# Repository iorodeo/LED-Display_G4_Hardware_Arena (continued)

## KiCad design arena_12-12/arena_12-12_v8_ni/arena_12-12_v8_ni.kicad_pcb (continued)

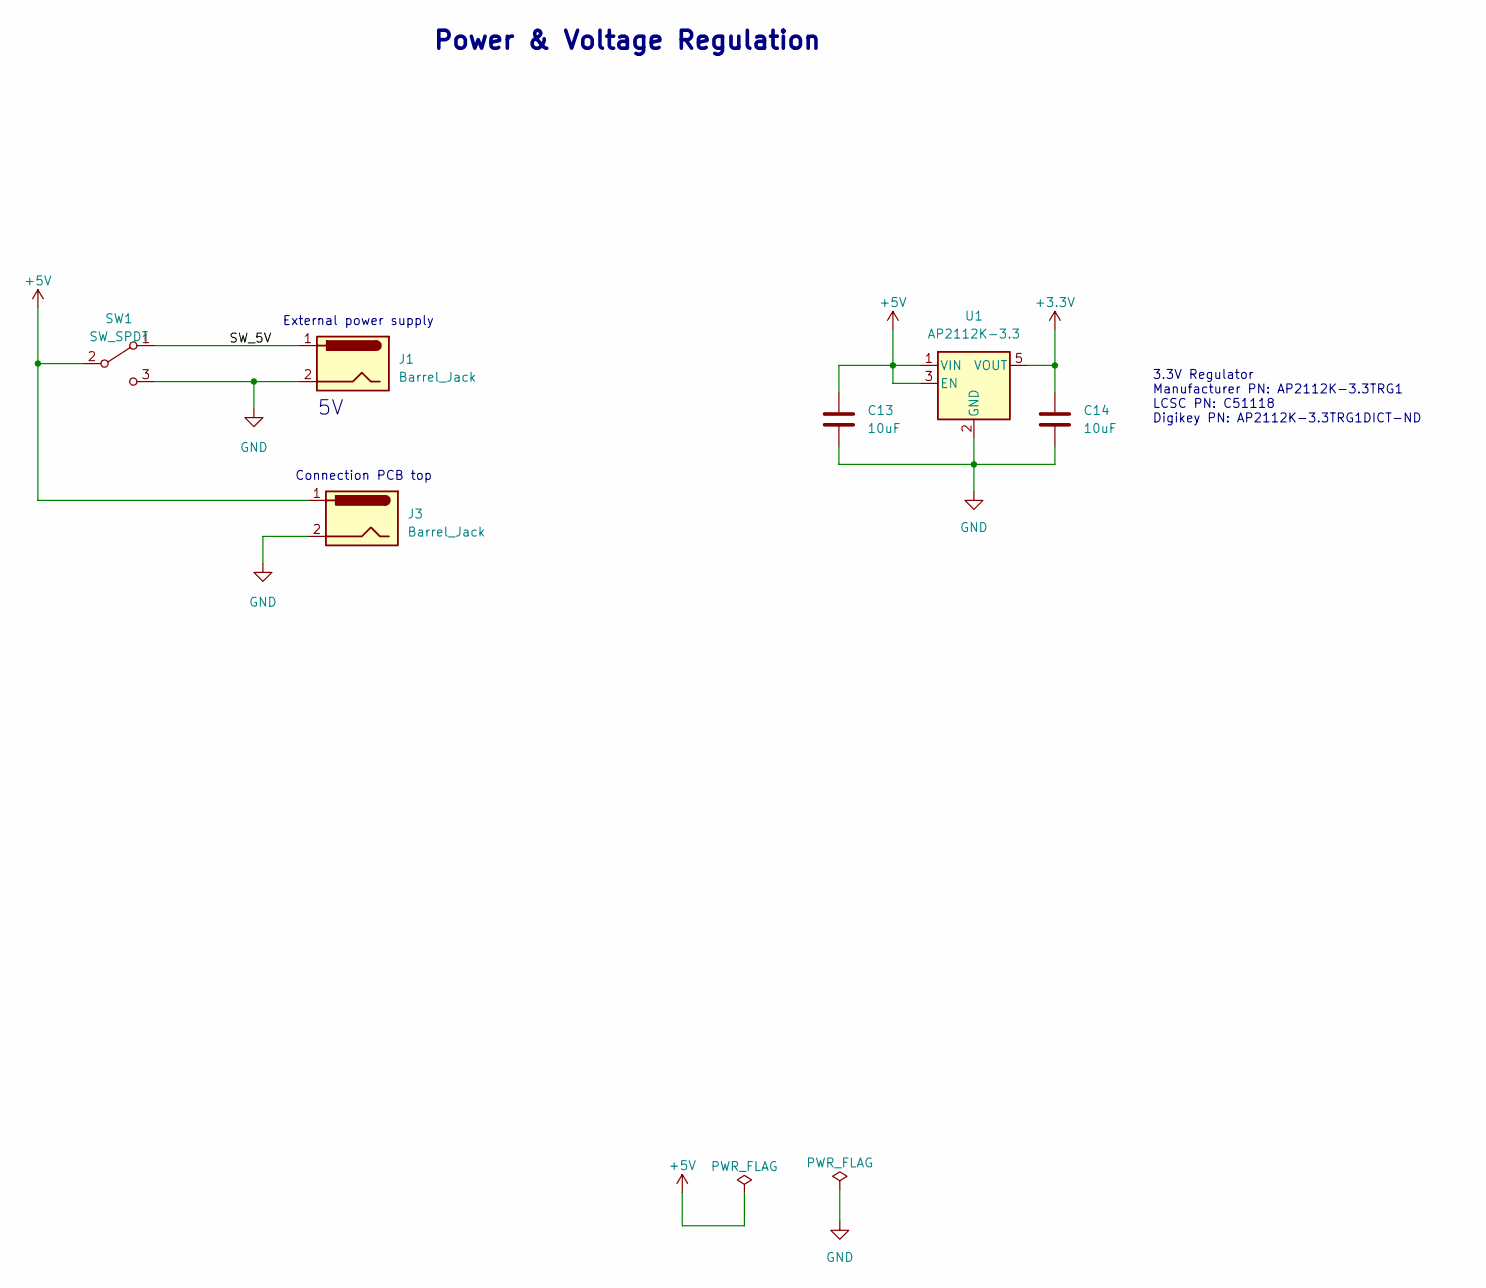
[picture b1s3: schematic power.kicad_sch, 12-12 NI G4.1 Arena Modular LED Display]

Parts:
C13, C14: 10uF; C_1206_3216Metric; MPN C3216X7R1C106KT000N; LCSC Part # C342827
J1, J3: Barrel_Jack; DCJACK_2PIN_HIGHCURRENT; MPN PJ-063AH; Digikey PN CP-063AH-ND
SW1: SW_SPDT; slide_switch; MPN L102021ML04Q; Digikey PN CKC5102-ND
U1: AP2112K-3.3; SOT-23-5; MPN AP2112K-3.3TRG1; Digikey PN AP2112K-3.3TRG1DICT-ND

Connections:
+3.3V: C14.1, U1.5 (VOUT); also elsewhere on the board
+5V: C13.1, J3.1, SW1.2 (B), U1.1 (VIN), U1.3 (EN); also elsewhere on the board
/Power & Voltage Regulators/SW_5V: J1.1, SW1.1 (A)
GND: C13.2, C14.2, J1.2, J3.2, SW1.3 (C), U1.2 (GND); also elsewhere on the board

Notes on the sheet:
External power supply
3.3V Regulator Manufacturer PN: AP2112K-3.3TRG1 LCSC PN: C51118 Digikey PN: AP2112K-3.3TRG1DICT-ND
Power & Voltage Regulation
Connection PCB top

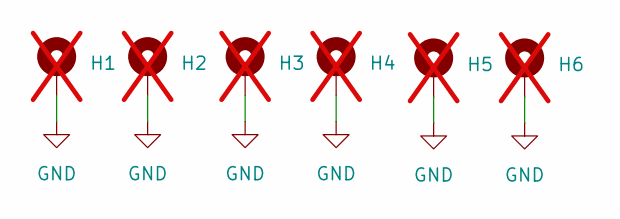
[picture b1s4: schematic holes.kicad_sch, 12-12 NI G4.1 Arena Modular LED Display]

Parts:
H1, H2, H3, H4, H5, H6: MountingHole_Pad; MountingHole_4.5mm_Pad; not fitted

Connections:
GND: H1.1, H2.1, H3.1, H4.1, H5.1, H6.1; also elsewhere on the board

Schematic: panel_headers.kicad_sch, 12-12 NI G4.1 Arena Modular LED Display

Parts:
C1, C2, C3, C4, C5, C6, C7, C8, C9, C10, C11, C12: 100uF; C_1210_3225Metric; MPN HGC1210R5107M160NSVK; LCSC Part # C7432790
C35, C36, C37, C38, C39, C40, C41, C42, C43, C44, C45, C46, C47, C48, C49, C50, C51, C52, C53, C54, C55, C56, C57, C58, C59, C60, C61, C62, C63, C64, C65, C66, C67, C68, C69, C70, C71, C72, C73, C74, C75, C76, C77, C78, C79, C80, C81, C82, C83, C84, C85, C86, C87, C88, C89, C90, C91, C92, C93, C94, C95, C96, C97, C98, C99, C100, C101, C102, C103, C104, C105, C106: 0.1uF; C_0402_1005Metric; MPN CL05B104KO5NNNC; LCSC Part # C1525
P1, P2, P3, P4, P5, P6, P7, P8, P9, P10, P11, P12: CONN15; HEADER_TOP; MPN PPPC151LFBN-RC; Digikey PN S7048-ND
Q1: MOSFET_NCHAN; SOT-23-3; MPN ME2306D; LCSC Part # C165220
R163, R164, R165, R166, R167, R168, R169, R170, R171, R172, R173, R174, R175, R176, R177, R178, R179, R180, R181, R182, R183, R184, R185, R186, R187, R188, R189, R190, R191, R192, R193, R194, R195, R196, R197, R198, R199, R200, R201, R202, R203, R204, R205, R206, R207, R208, R209, R210, R211, R212, R213, R214, R215, R216, R217, R218, R219, R220, R221, R222, R223, R224, R225, R226, R227, R228, R229, R230, R231, R232, R233, R234, R235, R236, R237, R238, R239, R240, R241, R242, R243, R244, R245, R246, R247, R248, R249, R250, R251, R252, R253, R254, R255, R256, R257, R258, R259, R260, R261, R262, R263, R264, R265, R266, R267, R268, R269, R270, R271, R272, R273, R274, R275, R276, R277, R278, R279, R280, R281, R282, R283, R284, R285, R286, R287, R288, R289, R290, R291, R292, R293, R294, R295, R296, R297, R298, R299, R300, R301, R302, R303, R304, R305, R306: 33; R_0402_1005Metric; MPN 0402WGF330JTCE; LCSC Part # C25105
R307: 20k; R_0402_1005Metric; MPN 0402WGF2002TCE; LCSC Part # C25765
R308: 200; R_0402_1005Metric; MPN 0402WGF2000TCE; LCSC Part # C25087
U39, U40, U41, U42, U43, U44, U45, U46, U47, U48, U49, U50, U51, U52, U53, U54, U55, U56, U57, U58, U59, U60, U61, U62, U63, U64, U65, U66, U67, U68, U69, U70, U71, U72, U73, U74, U75, U76, U77, U78, U79, U80, U81, U82, U83, U84, U85, U86, U87, U88, U89, U90, U91, U92, U93, U94, U95, U96, U97, U98, U99, U100, U101, U102, U103, U104, U105, U106, U107, U108, U109, U110: 74LVC2G17; SOT-23-6; MPN SN74LVC2G17DBVR; Digikey PN 296-SN74LVC2G17DBVRTR-ND

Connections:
+5V: C1.1, C2.1, C3.1, C4.1, C5.1, C6.1, C7.1, C8.1, C9.1, C10.1, C11.1, C12.1, C35.1, C36.1, C37.1, C38.1, C39.1, C40.1, C41.1, C42.1, C43.1, C44.1, C45.1, C46.1, C47.1, C48.1, C49.1, C50.1, C51.1, C52.1, C53.1, C54.1, C55.1, C56.1, C57.1, C58.1, C59.1, C60.1, C61.1, C62.1, C63.1, C64.1, C65.1, C66.1, C67.1, C68.1, C69.1, C70.1, C71.1, C72.1, C73.1, C74.1, C75.1, C76.1, C77.1, C78.1, C79.1, C80.1, C81.1, C82.1, C83.1, C84.1, C85.1, C86.1, C87.1, C88.1, C89.1, C90.1, C91.1, C92.1, C93.1, C94.1, C95.1, C96.1, C97.1, C98.1, C99.1, C100.1, C101.1, C102.1, C103.1, C104.1, C105.1, C106.1, P1.1, P2.1, P3.1, P4.1, P5.1, P6.1, P7.1, P8.1, P9.1, P10.1, P11.1, P12.1, U39.5 (VCC), U40.5 (VCC), U41.5 (VCC), U42.5 (VCC), U43.5 (VCC), U44.5 (VCC), U45.5 (VCC), U46.5 (VCC), U47.5 (VCC), U48.5 (VCC), U49.5 (VCC), U50.5 (VCC), U51.5 (VCC), U52.5 (VCC), U53.5 (VCC), U54.5 (VCC), U55.5 (VCC), U56.5 (VCC), U57.5 (VCC), U58.5 (VCC), U59.5 (VCC), U60.5 (VCC), U61.5 (VCC), U62.5 (VCC), U63.5 (VCC), U64.5 (VCC), U65.5 (VCC), U66.5 (VCC), U67.5 (VCC), U68.5 (VCC), U69.5 (VCC), U70.5 (VCC), U71.5 (VCC), U72.5 (VCC), U73.5 (VCC), U74.5 (VCC), U75.5 (VCC), U76.5 (VCC), U77.5 (VCC), U78.5 (VCC), U79.5 (VCC), U80.5 (VCC), U81.5 (VCC), U82.5 (VCC), U83.5 (VCC), U84.5 (VCC), U85.5 (VCC), U86.5 (VCC), U87.5 (VCC), U88.5 (VCC), U89.5 (VCC), U90.5 (VCC), U91.5 (VCC), U92.5 (VCC), U93.5 (VCC), U94.5 (VCC), U95.5 (VCC), U96.5 (VCC), U97.5 (VCC), U98.5 (VCC), U99.5 (VCC), U100.5 (VCC), U101.5 (VCC), U102.5 (VCC), U103.5 (VCC), U104.5 (VCC), U105.5 (VCC), U106.5 (VCC), U107.5 (VCC), U108.5 (VCC), U109.5 (VCC), U110.5 (VCC); also elsewhere on the board
/Level Shifters/PAN5V.CS_0_P01: U40.3; also elsewhere on the board
/Level Shifters/PAN5V.CS_0_P02: U46.3; also elsewhere on the board
/Level Shifters/PAN5V.CS_0_P03: U52.3; also elsewhere on the board
/Level Shifters/PAN5V.CS_0_P04: U58.3; also elsewhere on the board
/Level Shifters/PAN5V.CS_0_P05: U64.3; also elsewhere on the board
/Level Shifters/PAN5V.CS_0_P06: U70.3; also elsewhere on the board
/Level Shifters/PAN5V.CS_0_P07: U76.3; also elsewhere on the board
/Level Shifters/PAN5V.CS_0_P08: U82.3; also elsewhere on the board
/Level Shifters/PAN5V.CS_0_P09: U88.3; also elsewhere on the board
/Level Shifters/PAN5V.CS_0_P10: U94.3; also elsewhere on the board
/Level Shifters/PAN5V.CS_0_P11: U100.3; also elsewhere on the board
/Level Shifters/PAN5V.CS_0_P12: U106.3; also elsewhere on the board
/Level Shifters/PAN5V.CS_1_P01: U40.1; also elsewhere on the board
/Level Shifters/PAN5V.CS_1_P02: U46.1; also elsewhere on the board
/Level Shifters/PAN5V.CS_1_P03: U52.1; also elsewhere on the board
/Level Shifters/PAN5V.CS_1_P04: U58.1; also elsewhere on the board
/Level Shifters/PAN5V.CS_1_P05: U64.1; also elsewhere on the board
/Level Shifters/PAN5V.CS_1_P06: U70.1; also elsewhere on the board
/Level Shifters/PAN5V.CS_1_P07: U76.1; also elsewhere on the board
/Level Shifters/PAN5V.CS_1_P08: U82.1; also elsewhere on the board
/Level Shifters/PAN5V.CS_1_P09: U88.1; also elsewhere on the board
/Level Shifters/PAN5V.CS_1_P10: U94.1; also elsewhere on the board
/Level Shifters/PAN5V.CS_1_P11: U100.1; also elsewhere on the board
/Level Shifters/PAN5V.CS_1_P12: U106.1; also elsewhere on the board
/Level Shifters/PAN5V.CS_2_P01: U41.3; also elsewhere on the board
/Level Shifters/PAN5V.CS_2_P02: U47.3; also elsewhere on the board
/Level Shifters/PAN5V.CS_2_P03: U53.3; also elsewhere on the board
/Level Shifters/PAN5V.CS_2_P04: U59.3; also elsewhere on the board
/Level Shifters/PAN5V.CS_2_P05: U65.3; also elsewhere on the board
/Level Shifters/PAN5V.CS_2_P06: U71.3; also elsewhere on the board
/Level Shifters/PAN5V.CS_2_P07: U77.3; also elsewhere on the board
/Level Shifters/PAN5V.CS_2_P08: U83.3; also elsewhere on the board
/Level Shifters/PAN5V.CS_2_P09: U89.3; also elsewhere on the board
/Level Shifters/PAN5V.CS_2_P10: U95.3; also elsewhere on the board
/Level Shifters/PAN5V.CS_2_P11: U101.3; also elsewhere on the board
/Level Shifters/PAN5V.CS_2_P12: U107.3; also elsewhere on the board
/Level Shifters/PAN5V.CS_3_P01: U41.1; also elsewhere on the board
/Level Shifters/PAN5V.CS_3_P02: U47.1; also elsewhere on the board
/Level Shifters/PAN5V.CS_3_P03: U53.1; also elsewhere on the board
/Level Shifters/PAN5V.CS_3_P04: U59.1; also elsewhere on the board
/Level Shifters/PAN5V.CS_3_P05: U65.1; also elsewhere on the board
/Level Shifters/PAN5V.CS_3_P06: U71.1; also elsewhere on the board
/Level Shifters/PAN5V.CS_3_P07: U77.1; also elsewhere on the board
/Level Shifters/PAN5V.CS_3_P08: U83.1; also elsewhere on the board
/Level Shifters/PAN5V.CS_3_P09: U89.1; also elsewhere on the board
/Level Shifters/PAN5V.CS_3_P10: U95.1; also elsewhere on the board
/Level Shifters/PAN5V.CS_3_P11: U101.1; also elsewhere on the board
/Level Shifters/PAN5V.CS_3_P12: U107.1; also elsewhere on the board
/Level Shifters/PAN5V.CS_4_P01: U42.3; also elsewhere on the board
/Level Shifters/PAN5V.CS_4_P02: U48.3; also elsewhere on the board
/Level Shifters/PAN5V.CS_4_P03: U54.3; also elsewhere on the board
/Level Shifters/PAN5V.CS_4_P04: U60.3; also elsewhere on the board
/Level Shifters/PAN5V.CS_4_P05: U66.3; also elsewhere on the board
/Level Shifters/PAN5V.CS_4_P06: U72.3; also elsewhere on the board
/Level Shifters/PAN5V.CS_4_P07: U78.3; also elsewhere on the board
/Level Shifters/PAN5V.CS_4_P08: U84.3; also elsewhere on the board
/Level Shifters/PAN5V.CS_4_P09: U90.3; also elsewhere on the board
/Level Shifters/PAN5V.CS_4_P10: U96.3; also elsewhere on the board
/Level Shifters/PAN5V.CS_4_P11: U102.3; also elsewhere on the board
/Level Shifters/PAN5V.CS_4_P12: U108.3; also elsewhere on the board
/Level Shifters/PAN5V.CS_5_P01: U42.1; also elsewhere on the board
/Level Shifters/PAN5V.CS_5_P02: U48.1; also elsewhere on the board
/Level Shifters/PAN5V.CS_5_P03: U54.1; also elsewhere on the board
/Level Shifters/PAN5V.CS_5_P04: U60.1; also elsewhere on the board
/Level Shifters/PAN5V.CS_5_P05: U66.1; also elsewhere on the board
/Level Shifters/PAN5V.CS_5_P06: U72.1; also elsewhere on the board
/Level Shifters/PAN5V.CS_5_P07: U78.1; also elsewhere on the board
/Level Shifters/PAN5V.CS_5_P08: U84.1; also elsewhere on the board
/Level Shifters/PAN5V.CS_5_P09: U90.1; also elsewhere on the board
/Level Shifters/PAN5V.CS_5_P10: U96.1; also elsewhere on the board
/Level Shifters/PAN5V.CS_5_P11: U102.1; also elsewhere on the board
/Level Shifters/PAN5V.CS_5_P12: U108.1; also elsewhere on the board
/Level Shifters/PAN5V.CS_6_P01: U43.3; also elsewhere on the board
/Level Shifters/PAN5V.CS_6_P02: U49.3; also elsewhere on the board
/Level Shifters/PAN5V.CS_6_P03: U55.3; also elsewhere on the board
/Level Shifters/PAN5V.CS_6_P04: U61.3; also elsewhere on the board
/Level Shifters/PAN5V.CS_6_P05: U67.3; also elsewhere on the board
/Level Shifters/PAN5V.CS_6_P06: U73.3; also elsewhere on the board
/Level Shifters/PAN5V.CS_6_P07: U79.3; also elsewhere on the board
/Level Shifters/PAN5V.CS_6_P08: U85.3; also elsewhere on the board
/Level Shifters/PAN5V.CS_6_P09: U91.3; also elsewhere on the board
/Level Shifters/PAN5V.CS_6_P10: U97.3; also elsewhere on the board
/Level Shifters/PAN5V.CS_6_P11: U103.3; also elsewhere on the board
/Level Shifters/PAN5V.CS_6_P12: U109.3; also elsewhere on the board
/Level Shifters/PAN5V.CS_7_P01: U43.1; also elsewhere on the board
/Level Shifters/PAN5V.CS_7_P02: U49.1; also elsewhere on the board
/Level Shifters/PAN5V.CS_7_P03: U55.1; also elsewhere on the board
/Level Shifters/PAN5V.CS_7_P04: U61.1; also elsewhere on the board
/Level Shifters/PAN5V.CS_7_P05: U67.1; also elsewhere on the board
/Level Shifters/PAN5V.CS_7_P06: U73.1; also elsewhere on the board
/Level Shifters/PAN5V.CS_7_P07: U79.1; also elsewhere on the board
/Level Shifters/PAN5V.CS_7_P08: U85.1; also elsewhere on the board
/Level Shifters/PAN5V.CS_7_P09: U91.1; also elsewhere on the board
/Level Shifters/PAN5V.CS_7_P10: U97.1; also elsewhere on the board
/Level Shifters/PAN5V.CS_7_P11: U103.1; also elsewhere on the board
/Level Shifters/PAN5V.CS_7_P12: U109.1; also elsewhere on the board
/Level Shifters/PAN5V.EXT_INT: U44.3, U50.3, U56.3, U62.3, U68.3, U74.3, U80.3, U86.3, U92.3, U98.3, U104.3, U110.3; also elsewhere on the board
/Level Shifters/PAN5V.MISO_00: R165.1; also elsewhere on the board
/Level Shifters/PAN5V.MISO_01: R177.1; also elsewhere on the board
/Level Shifters/PAN5V.MISO_02: R189.1; also elsewhere on the board
/Level Shifters/PAN5V.MISO_03: R201.1; also elsewhere on the board
/Level Shifters/PAN5V.MISO_04: R213.1; also elsewhere on the board
/Level Shifters/PAN5V.MISO_05: R225.1; also elsewhere on the board
/Level Shifters/PAN5V.MISO_06: R237.1; also elsewhere on the board
/Level Shifters/PAN5V.MISO_07: R249.1; also elsewhere on the board
/Level Shifters/PAN5V.MISO_08: R261.1; also elsewhere on the board
/Level Shifters/PAN5V.MISO_09: R273.1; also elsewhere on the board
/Level Shifters/PAN5V.MISO_10: R285.1; also elsewhere on the board
/Level Shifters/PAN5V.MISO_11: R297.1; also elsewhere on the board
/Level Shifters/PAN5V.MOSI_00: U39.1; also elsewhere on the board
/Level Shifters/PAN5V.MOSI_01: U45.1; also elsewhere on the board
/Level Shifters/PAN5V.MOSI_02: U51.1; also elsewhere on the board
/Level Shifters/PAN5V.MOSI_03: U57.1; also elsewhere on the board
/Level Shifters/PAN5V.MOSI_04: U63.1; also elsewhere on the board
/Level Shifters/PAN5V.MOSI_05: U69.1; also elsewhere on the board
/Level Shifters/PAN5V.MOSI_06: U75.1; also elsewhere on the board
/Level Shifters/PAN5V.MOSI_07: U81.1; also elsewhere on the board
/Level Shifters/PAN5V.MOSI_08: U87.1; also elsewhere on the board
/Level Shifters/PAN5V.MOSI_09: U93.1; also elsewhere on the board
/Level Shifters/PAN5V.MOSI_10: U99.1; also elsewhere on the board
/Level Shifters/PAN5V.MOSI_11: U105.1; also elsewhere on the board
/Level Shifters/PAN5V.RESET: R308.2; also elsewhere on the board
/Level Shifters/PAN5V.SCK_0_H1: U39.3; also elsewhere on the board
/Level Shifters/PAN5V.SCK_0_H2: U75.3; also elsewhere on the board
/Level Shifters/PAN5V.SCK_1_H1: U45.3; also elsewhere on the board
/Level Shifters/PAN5V.SCK_1_H2: U81.3; also elsewhere on the board
/Level Shifters/PAN5V.SCK_2_H1: U51.3; also elsewhere on the board
/Level Shifters/PAN5V.SCK_2_H2: U87.3; also elsewhere on the board
/Level Shifters/PAN5V.SCK_3_H1: U57.3; also elsewhere on the board
/Level Shifters/PAN5V.SCK_3_H2: U93.3; also elsewhere on the board
/Level Shifters/PAN5V.SCK_4_H1: U63.3; also elsewhere on the board
/Level Shifters/PAN5V.SCK_4_H2: U99.3; also elsewhere on the board
/Level Shifters/PAN5V.SCK_5_H1: U69.3; also elsewhere on the board
/Level Shifters/PAN5V.SCK_5_H2: U105.3; also elsewhere on the board
/Panel Headers/CS_00_P01: P1.7, R166.2
/Panel Headers/CS_00_P02: P2.7, R178.2
/Panel Headers/CS_00_P03: P3.7, R190.2
/Panel Headers/CS_00_P04: P4.7, R202.2
/Panel Headers/CS_00_P05: P5.7, R214.2
/Panel Headers/CS_00_P06: P6.7, R226.2
/Panel Headers/CS_00_P07: P7.7, R238.2
/Panel Headers/CS_00_P08: P8.7, R250.2
/Panel Headers/CS_00_P09: P9.7, R262.2
/Panel Headers/CS_00_P10: P10.7, R274.2
/Panel Headers/CS_00_P11: P11.7, R286.2
/Panel Headers/CS_00_P12: P12.7, R298.2
/Panel Headers/CS_01_P01: P1.8, R167.2
/Panel Headers/CS_01_P02: P2.8, R179.2
/Panel Headers/CS_01_P03: P3.8, R191.2
/Panel Headers/CS_01_P04: P4.8, R203.2
/Panel Headers/CS_01_P05: P5.8, R215.2
/Panel Headers/CS_01_P06: P6.8, R227.2
/Panel Headers/CS_01_P07: P7.8, R239.2
/Panel Headers/CS_01_P08: P8.8, R251.2
/Panel Headers/CS_01_P09: P9.8, R263.2
/Panel Headers/CS_01_P10: P10.8, R275.2
/Panel Headers/CS_01_P11: P11.8, R287.2
/Panel Headers/CS_01_P12: P12.8, R299.2
/Panel Headers/CS_02_P01: P1.9, R168.2
/Panel Headers/CS_02_P02: P2.9, R180.2
/Panel Headers/CS_02_P03: P3.9, R192.2
/Panel Headers/CS_02_P04: P4.9, R204.2
/Panel Headers/CS_02_P05: P5.9, R216.2
/Panel Headers/CS_02_P06: P6.9, R228.2
/Panel Headers/CS_02_P07: P7.9, R240.2
/Panel Headers/CS_02_P08: P8.9, R252.2
/Panel Headers/CS_02_P09: P9.9, R264.2
/Panel Headers/CS_02_P10: P10.9, R276.2
/Panel Headers/CS_02_P11: P11.9, R288.2
/Panel Headers/CS_02_P12: P12.9, R300.2
/Panel Headers/CS_03_P01: P1.10, R169.2
/Panel Headers/CS_03_P02: P2.10, R181.2
/Panel Headers/CS_03_P03: P3.10, R193.2
/Panel Headers/CS_03_P04: P4.10, R205.2
/Panel Headers/CS_03_P05: P5.10, R217.2
/Panel Headers/CS_03_P06: P6.10, R229.2
/Panel Headers/CS_03_P07: P7.10, R241.2
/Panel Headers/CS_03_P08: P8.10, R253.2
/Panel Headers/CS_03_P09: P9.10, R265.2
/Panel Headers/CS_03_P10: P10.10, R277.2
/Panel Headers/CS_03_P11: P11.10, R289.2
/Panel Headers/CS_03_P12: P12.10, R301.2
/Panel Headers/CS_04_P01: P1.11, R170.2
/Panel Headers/CS_04_P02: P2.11, R182.2
/Panel Headers/CS_04_P03: P3.11, R194.2
/Panel Headers/CS_04_P04: P4.11, R206.2
/Panel Headers/CS_04_P05: P5.11, R218.2
/Panel Headers/CS_04_P06: P6.11, R230.2
/Panel Headers/CS_04_P07: P7.11, R242.2
/Panel Headers/CS_04_P08: P8.11, R254.2
/Panel Headers/CS_04_P09: P9.11, R266.2
/Panel Headers/CS_04_P10: P10.11, R278.2
/Panel Headers/CS_04_P11: P11.11, R290.2
/Panel Headers/CS_04_P12: P12.11, R302.2
/Panel Headers/CS_05_P01: P1.12, R171.2
/Panel Headers/CS_05_P02: P2.12, R183.2
/Panel Headers/CS_05_P03: P3.12, R195.2
/Panel Headers/CS_05_P04: P4.12, R207.2
/Panel Headers/CS_05_P05: P5.12, R219.2
/Panel Headers/CS_05_P06: P6.12, R231.2
/Panel Headers/CS_05_P07: P7.12, R243.2
/Panel Headers/CS_05_P08: P8.12, R255.2
/Panel Headers/CS_05_P09: P9.12, R267.2
/Panel Headers/CS_05_P10: P10.12, R279.2
/Panel Headers/CS_05_P11: P11.12, R291.2
/Panel Headers/CS_05_P12: P12.12, R303.2
/Panel Headers/CS_06_P01: P1.13, R172.2
/Panel Headers/CS_06_P02: P2.13, R184.2
/Panel Headers/CS_06_P03: P3.13, R196.2
/Panel Headers/CS_06_P04: P4.13, R208.2
/Panel Headers/CS_06_P05: P5.13, R220.2
/Panel Headers/CS_06_P06: P6.13, R232.2
/Panel Headers/CS_06_P07: P7.13, R244.2
/Panel Headers/CS_06_P08: P8.13, R256.2
/Panel Headers/CS_06_P09: P9.13, R268.2
/Panel Headers/CS_06_P10: P10.13, R280.2
/Panel Headers/CS_06_P11: P11.13, R292.2
/Panel Headers/CS_06_P12: P12.13, R304.2
/Panel Headers/CS_07_P01: P1.14, R173.2
/Panel Headers/CS_07_P02: P2.14, R185.2
/Panel Headers/CS_07_P03: P3.14, R197.2
/Panel Headers/CS_07_P04: P4.14, R209.2
/Panel Headers/CS_07_P05: P5.14, R221.2
/Panel Headers/CS_07_P06: P6.14, R233.2
/Panel Headers/CS_07_P07: P7.14, R245.2
/Panel Headers/CS_07_P08: P8.14, R257.2
/Panel Headers/CS_07_P09: P9.14, R269.2
/Panel Headers/CS_07_P10: P10.14, R281.2
/Panel Headers/CS_07_P11: P11.14, R293.2
/Panel Headers/CS_07_P12: P12.14, R305.2
/Panel Headers/EXT_INT_P01: P1.15, R174.2
/Panel Headers/EXT_INT_P02: P2.15, R186.2
/Panel Headers/EXT_INT_P03: P3.15, R198.2
/Panel Headers/EXT_INT_P04: P4.15, R210.2
/Panel Headers/EXT_INT_P05: P5.15, R222.2
/Panel Headers/EXT_INT_P06: P6.15, R234.2
/Panel Headers/EXT_INT_P07: P7.15, R246.2
/Panel Headers/EXT_INT_P08: P8.15, R258.2
/Panel Headers/EXT_INT_P09: P9.15, R270.2
/Panel Headers/EXT_INT_P10: P10.15, R282.2
/Panel Headers/EXT_INT_P11: P11.15, R294.2
/Panel Headers/EXT_INT_P12: P12.15, R306.2
/Panel Headers/MISO_00_P01: P1.6, R165.2
/Panel Headers/MISO_01_P02: P2.6, R177.2
/Panel Headers/MISO_02_P03: P3.6, R189.2
/Panel Headers/MISO_03_P04: P4.6, R201.2
/Panel Headers/MISO_04_P05: P5.6, R213.2
/Panel Headers/MISO_05_P06: P6.6, R225.2
/Panel Headers/MISO_06_P07: P7.6, R237.2
/Panel Headers/MISO_07_P08: P8.6, R249.2
/Panel Headers/MISO_08_P09: P9.6, R261.2
/Panel Headers/MISO_09_P10: P10.6, R273.2
/Panel Headers/MISO_10_P11: P11.6, R285.2
/Panel Headers/MISO_11_P12: P12.6, R297.2
/Panel Headers/MOSI_00_P01: P1.5, R164.2
/Panel Headers/MOSI_01_P02: P2.5, R176.2
/Panel Headers/MOSI_02_P03: P3.5, R188.2
/Panel Headers/MOSI_03_P04: P4.5, R200.2
/Panel Headers/MOSI_04_P05: P5.5, R212.2
/Panel Headers/MOSI_05_P06: P6.5, R224.2
/Panel Headers/MOSI_06_P07: P7.5, R236.2
/Panel Headers/MOSI_07_P08: P8.5, R248.2
/Panel Headers/MOSI_08_P09: P9.5, R260.2
/Panel Headers/MOSI_09_P10: P10.5, R272.2
/Panel Headers/MOSI_10_P11: P11.5, R284.2
/Panel Headers/MOSI_11_P12: P12.5, R296.2
/Panel Headers/RESET: P1.3, P2.3, P3.3, P4.3, P5.3, P6.3, P7.3, P8.3, P9.3, P10.3, P11.3, P12.3, Q1.3 (D)
/Panel Headers/SCK_0_H1_P01: P1.4, R163.2
/Panel Headers/SCK_0_H2_P07: P7.4, R235.2
/Panel Headers/SCK_1_H1_P02: P2.4, R175.2
/Panel Headers/SCK_1_H2_P08: P8.4, R247.2
/Panel Headers/SCK_2_H1_P03: P3.4, R187.2
/Panel Headers/SCK_2_H2_P09: P9.4, R259.2
/Panel Headers/SCK_3_H1_P04: P4.4, R199.2
/Panel Headers/SCK_3_H2_P10: P10.4, R271.2
/Panel Headers/SCK_4_H1_P05: P5.4, R211.2
/Panel Headers/SCK_4_H2_P11: P11.4, R283.2
/Panel Headers/SCK_5_H1_P06: P6.4, R223.2
/Panel Headers/SCK_5_H2_P12: P12.4, R295.2
GND: C1.2, C2.2, C3.2, C4.2, C5.2, C6.2, C7.2, C8.2, C9.2, C10.2, C11.2, C12.2, C35.2, C36.2, C37.2, C38.2, C39.2, C40.2, C41.2, C42.2, C43.2, C44.2, C45.2, C46.2, C47.2, C48.2, C49.2, C50.2, C51.2, C52.2, C53.2, C54.2, C55.2, C56.2, C57.2, C58.2, C59.2, C60.2, C61.2, C62.2, C63.2, C64.2, C65.2, C66.2, C67.2, C68.2, C69.2, C70.2, C71.2, C72.2, C73.2, C74.2, C75.2, C76.2, C77.2, C78.2, C79.2, C80.2, C81.2, C82.2, C83.2, C84.2, C85.2, C86.2, C87.2, C88.2, C89.2, C90.2, C91.2, C92.2, C93.2, C94.2, C95.2, C96.2, C97.2, C98.2, C99.2, C100.2, C101.2, C102.2, C103.2, C104.2, C105.2, C106.2, P1.2, P2.2, P3.2, P4.2, P5.2, P6.2, P7.2, P8.2, P9.2, P10.2, P11.2, P12.2, Q1.2 (S), R307.1, U39.2 (GND), U40.2 (GND), U41.2 (GND), U42.2 (GND), U43.2 (GND), U44.2 (GND), U45.2 (GND), U46.2 (GND), U47.2 (GND), U48.2 (GND), U49.2 (GND), U50.2 (GND), U51.2 (GND), U52.2 (GND), U53.2 (GND), U54.2 (GND), U55.2 (GND), U56.2 (GND), U57.2 (GND), U58.2 (GND), U59.2 (GND), U60.2 (GND), U61.2 (GND), U62.2 (GND), U63.2 (GND), U64.2 (GND), U65.2 (GND), U66.2 (GND), U67.2 (GND), U68.2 (GND), U69.2 (GND), U70.2 (GND), U71.2 (GND), U72.2 (GND), U73.2 (GND), U74.2 (GND), U75.2 (GND), U76.2 (GND), U77.2 (GND), U78.2 (GND), U79.2 (GND), U80.2 (GND), U81.2 (GND), U82.2 (GND), U83.2 (GND), U84.2 (GND), U85.2 (GND), U86.2 (GND), U87.2 (GND), U88.2 (GND), U89.2 (GND), U90.2 (GND), U91.2 (GND), U92.2 (GND), U93.2 (GND), U94.2 (GND), U95.2 (GND), U96.2 (GND), U97.2 (GND), U98.2 (GND), U99.2 (GND), U100.2 (GND), U101.2 (GND), U102.2 (GND), U103.2 (GND), U104.2 (GND), U105.2 (GND), U106.2 (GND), U107.2 (GND), U108.2 (GND), U109.2 (GND), U110.2 (GND); also elsewhere on the board
unnamed: Q1.1 (G), R307.2, R308.1
unnamed: R163.1, U39.4
unnamed: R164.1, U39.6
unnamed: R166.1, U40.4
unnamed: R167.1, U40.6
unnamed: R168.1, U41.4
unnamed: R169.1, U41.6
unnamed: R170.1, U42.4
unnamed: R171.1, U42.6
unnamed: R172.1, U43.4
unnamed: R173.1, U43.6
unnamed: R174.1, U44.4
unnamed: R175.1, U45.4
unnamed: R176.1, U45.6
unnamed: R178.1, U46.4
unnamed: R179.1, U46.6
unnamed: R180.1, U47.4
unnamed: R181.1, U47.6
unnamed: R182.1, U48.4
unnamed: R183.1, U48.6
unnamed: R184.1, U49.4
unnamed: R185.1, U49.6
unnamed: R186.1, U50.4
unnamed: R187.1, U51.4
unnamed: R188.1, U51.6
unnamed: R190.1, U52.4
unnamed: R191.1, U52.6
unnamed: R192.1, U53.4
unnamed: R193.1, U53.6
unnamed: R194.1, U54.4
unnamed: R195.1, U54.6
unnamed: R196.1, U55.4
unnamed: R197.1, U55.6
unnamed: R198.1, U56.4
unnamed: R199.1, U57.4
unnamed: R200.1, U57.6
unnamed: R202.1, U58.4
unnamed: R203.1, U58.6
unnamed: R204.1, U59.4
unnamed: R205.1, U59.6
unnamed: R206.1, U60.4
unnamed: R207.1, U60.6
unnamed: R208.1, U61.4
unnamed: R209.1, U61.6
unnamed: R210.1, U62.4
unnamed: R211.1, U63.4
unnamed: R212.1, U63.6
unnamed: R214.1, U64.4
unnamed: R215.1, U64.6
unnamed: R216.1, U65.4
unnamed: R217.1, U65.6
unnamed: R218.1, U66.4
unnamed: R219.1, U66.6
unnamed: R220.1, U67.4
unnamed: R221.1, U67.6
unnamed: R222.1, U68.4
unnamed: R223.1, U69.4
unnamed: R224.1, U69.6
unnamed: R226.1, U70.4
unnamed: R227.1, U70.6
unnamed: R228.1, U71.4
unnamed: R229.1, U71.6
unnamed: R230.1, U72.4
unnamed: R231.1, U72.6
unnamed: R232.1, U73.4
unnamed: R233.1, U73.6
unnamed: R234.1, U74.4
unnamed: R235.1, U75.4
unnamed: R236.1, U75.6
unnamed: R238.1, U76.4
unnamed: R239.1, U76.6
unnamed: R240.1, U77.4
unnamed: R241.1, U77.6
unnamed: R242.1, U78.4
unnamed: R243.1, U78.6
unnamed: R244.1, U79.4
unnamed: R245.1, U79.6
unnamed: R246.1, U80.4
unnamed: R247.1, U81.4
unnamed: R248.1, U81.6
unnamed: R250.1, U82.4
unnamed: R251.1, U82.6
unnamed: R252.1, U83.4
unnamed: R253.1, U83.6
unnamed: R254.1, U84.4
unnamed: R255.1, U84.6
unnamed: R256.1, U85.4
unnamed: R257.1, U85.6
unnamed: R258.1, U86.4
unnamed: R259.1, U87.4
unnamed: R260.1, U87.6
unnamed: R262.1, U88.4
unnamed: R263.1, U88.6
unnamed: R264.1, U89.4
unnamed: R265.1, U89.6
unnamed: R266.1, U90.4
unnamed: R267.1, U90.6
unnamed: R268.1, U91.4
unnamed: R269.1, U91.6
unnamed: R270.1, U92.4
unnamed: R271.1, U93.4
unnamed: R272.1, U93.6
unnamed: R274.1, U94.4
unnamed: R275.1, U94.6
unnamed: R276.1, U95.4
unnamed: R277.1, U95.6
unnamed: R278.1, U96.4
unnamed: R279.1, U96.6
unnamed: R280.1, U97.4
unnamed: R281.1, U97.6
unnamed: R282.1, U98.4
unnamed: R283.1, U99.4
unnamed: R284.1, U99.6
unnamed: R286.1, U100.4
unnamed: R287.1, U100.6
unnamed: R288.1, U101.4
unnamed: R289.1, U101.6
unnamed: R290.1, U102.4
unnamed: R291.1, U102.6
unnamed: R292.1, U103.4
unnamed: R293.1, U103.6
unnamed: R294.1, U104.4
unnamed: R295.1, U105.4
unnamed: R296.1, U105.6
unnamed: R298.1, U106.4
unnamed: R299.1, U106.6
unnamed: R300.1, U107.4
unnamed: R301.1, U107.6
unnamed: R302.1, U108.4
unnamed: R303.1, U108.6
unnamed: R304.1, U109.4
unnamed: R305.1, U109.6
unnamed: R306.1, U110.4

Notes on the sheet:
Panel base capacitor: C7432790 16V 100uF
Panel Headers
SI2302-TP Digikey SI2302-TPMSCT-ND LCSC C4748714 or ME2306D LCSC C165220

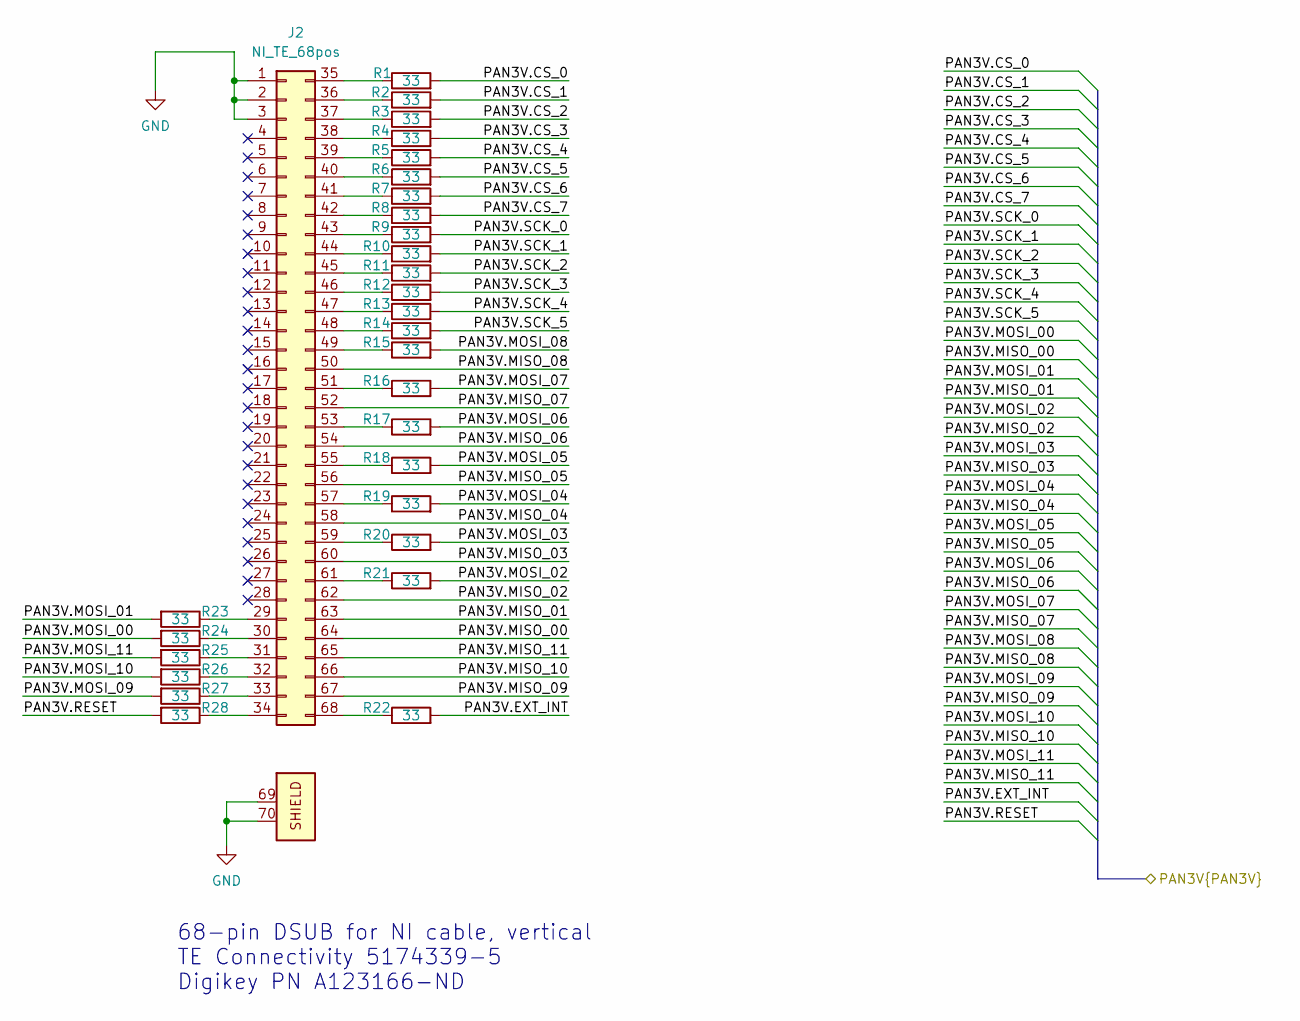
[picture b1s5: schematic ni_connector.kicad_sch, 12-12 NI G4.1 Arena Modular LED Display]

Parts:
J2: NI_TE_68pos; TE_CONN_DSUB_VERT_68; MPN 5174339-5; Digikey PN A123166-ND
R1, R2, R3, R4, R5, R6, R7, R8, R9, R10, R11, R12, R13, R14, R15, R16, R17, R18, R19, R20, R21, R22, R23, R24, R25, R26, R27, R28: 33; R_0402_1005Metric; MPN 0402WGF330JTCE; LCSC Part # C25105

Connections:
/Level Shifters/PAN3V.CS_0: R1.2; also elsewhere on the board
/Level Shifters/PAN3V.CS_1: R2.2; also elsewhere on the board
/Level Shifters/PAN3V.CS_2: R3.2; also elsewhere on the board
/Level Shifters/PAN3V.CS_3: R4.2; also elsewhere on the board
/Level Shifters/PAN3V.CS_4: R5.2; also elsewhere on the board
/Level Shifters/PAN3V.CS_5: R6.2; also elsewhere on the board
/Level Shifters/PAN3V.CS_6: R7.2; also elsewhere on the board
/Level Shifters/PAN3V.CS_7: R8.2; also elsewhere on the board
/Level Shifters/PAN3V.EXT_INT: R22.2; also elsewhere on the board
/Level Shifters/PAN3V.MISO_00: J2.64; also elsewhere on the board
/Level Shifters/PAN3V.MISO_01: J2.63; also elsewhere on the board
/Level Shifters/PAN3V.MISO_02: J2.62; also elsewhere on the board
/Level Shifters/PAN3V.MISO_03: J2.60; also elsewhere on the board
/Level Shifters/PAN3V.MISO_04: J2.58; also elsewhere on the board
/Level Shifters/PAN3V.MISO_05: J2.56; also elsewhere on the board
/Level Shifters/PAN3V.MISO_06: J2.54; also elsewhere on the board
/Level Shifters/PAN3V.MISO_07: J2.52; also elsewhere on the board
/Level Shifters/PAN3V.MISO_08: J2.50; also elsewhere on the board
/Level Shifters/PAN3V.MISO_09: J2.67; also elsewhere on the board
/Level Shifters/PAN3V.MISO_10: J2.66; also elsewhere on the board
/Level Shifters/PAN3V.MISO_11: J2.65; also elsewhere on the board
/Level Shifters/PAN3V.MOSI_00: R24.2; also elsewhere on the board
/Level Shifters/PAN3V.MOSI_01: R23.2; also elsewhere on the board
/Level Shifters/PAN3V.MOSI_02: R21.2; also elsewhere on the board
/Level Shifters/PAN3V.MOSI_03: R20.2; also elsewhere on the board
/Level Shifters/PAN3V.MOSI_04: R19.2; also elsewhere on the board
/Level Shifters/PAN3V.MOSI_05: R18.2; also elsewhere on the board
/Level Shifters/PAN3V.MOSI_06: R17.2; also elsewhere on the board
/Level Shifters/PAN3V.MOSI_07: R16.2; also elsewhere on the board
/Level Shifters/PAN3V.MOSI_08: R15.2; also elsewhere on the board
/Level Shifters/PAN3V.MOSI_09: R27.2; also elsewhere on the board
/Level Shifters/PAN3V.MOSI_10: R26.2; also elsewhere on the board
/Level Shifters/PAN3V.MOSI_11: R25.2; also elsewhere on the board
/Level Shifters/PAN3V.RESET: R28.2; also elsewhere on the board
/Level Shifters/PAN3V.SCK_0: R9.2; also elsewhere on the board
/Level Shifters/PAN3V.SCK_1: R10.2; also elsewhere on the board
/Level Shifters/PAN3V.SCK_2: R11.2; also elsewhere on the board
/Level Shifters/PAN3V.SCK_3: R12.2; also elsewhere on the board
/Level Shifters/PAN3V.SCK_4: R13.2; also elsewhere on the board
/Level Shifters/PAN3V.SCK_5: R14.2; also elsewhere on the board
GND: J2.1, J2.2, J2.3, J2.69 (GND), J2.70 (GND); also elsewhere on the board
unnamed: J2.29, R23.1
unnamed: J2.30, R24.1
unnamed: J2.31, R25.1
unnamed: J2.32, R26.1
unnamed: J2.33, R27.1
unnamed: J2.34, R28.1
unnamed: J2.35, R1.1
unnamed: J2.36, R2.1
unnamed: J2.37, R3.1
unnamed: J2.38, R4.1
unnamed: J2.39, R5.1
unnamed: J2.40, R6.1
unnamed: J2.41, R7.1
unnamed: J2.42, R8.1
unnamed: J2.43, R9.1
unnamed: J2.44, R10.1
unnamed: J2.45, R11.1
unnamed: J2.46, R12.1
unnamed: J2.47, R13.1
unnamed: J2.48, R14.1
unnamed: J2.49, R15.1
unnamed: J2.51, R16.1
unnamed: J2.53, R17.1
unnamed: J2.55, R18.1
unnamed: J2.57, R19.1
unnamed: J2.59, R20.1
unnamed: J2.61, R21.1
unnamed: J2.68, R22.1

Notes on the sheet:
68-pin DSUB for NI cable, vertical TE Connectivity 5174339-5 Digikey PN A123166-ND
